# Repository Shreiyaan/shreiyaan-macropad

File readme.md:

Shreiyaan’s Macropad

This is a three-key macropad with a rotary encoder. I made it for simple media controls and shortcuts that I use regularly. I designed the PCB in KiCad, made the enclosure in Fusion 360, and prepared the firmware using QMK.

The macropad uses a Seeed Studio XIAO RP2040, three MX-style mechanical switches, and an EC11 rotary encoder with a push switch.

The three keys are used for speaker mute, play/pause, and Print Screen. Rotating the encoder changes the volume, and pressing the encoder toggles speaker mute.

I made the enclosure slightly larger so the macropad has a stable base and enough space around the controls to be comfortable on a desk. (and also, so i can design cool things on the case to make it look good)

Schematic:

PCB:

Enclosure:

The folder contains the KiCad schematic and PCB, Gerber and drill files, the STEP enclosure model, BOM, firmware source, compiled UF2 firmware, DRC report and project images.

The PCB DRC has 0 errors and 0 unconnected items. The remaining warnings are mostly related to silkscreen overlapping solder-mask areas.

The firmware has not been tested on assembled hardware yet. I will test the keys and encoder after the PCB is manufactured and assembled.

Use manufacturing_final.zip for PCB manufacturing. It contains the updated Gerber and drill files exported from Macropad_Checked.kicad_pcb. The other Gerber files and manufacturing ZIP are older versions.

Made by Shreiyaan P Shah.

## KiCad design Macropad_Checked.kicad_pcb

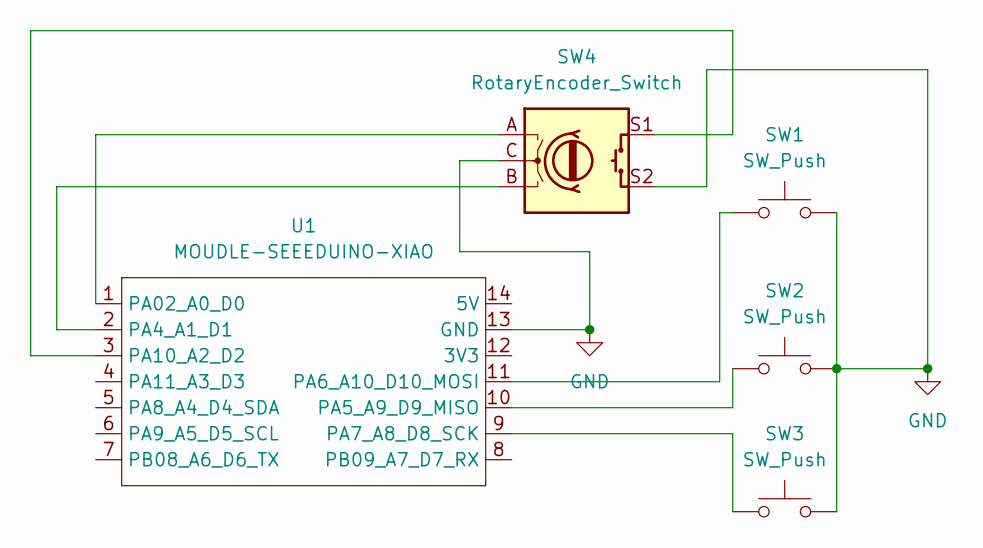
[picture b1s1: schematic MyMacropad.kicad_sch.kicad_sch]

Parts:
SW1, SW2, SW3: SW_Push; SW_Cherry_MX_1.00u_PCB
SW4: RotaryEncoder_Switch; RotaryEncoder_Alps_EC11E-Switch_Vertical_H20mm
U1: MOUDLE-SEEEDUINO-XIAO; XIAO-Generic-Hybrid-14P-2.54-21X17.8MM

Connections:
GND: SW1.2, SW2.2, SW3.2, SW4.C, SW4.S2, U1.13 (GND)
unnamed: SW4.A, U1.1 (PA02_A0_D0)
unnamed: SW4.B, U1.2 (PA4_A1_D1)
unnamed: SW2.1, U1.10 (PA5_A9_D9_MISO)
unnamed: SW1.1, U1.11 (PA6_A10_D10_MOSI)
unnamed: SW3.1, U1.9 (PA7_A8_D8_SCK)
unnamed: SW4.S1, U1.3 (PA10_A2_D2)

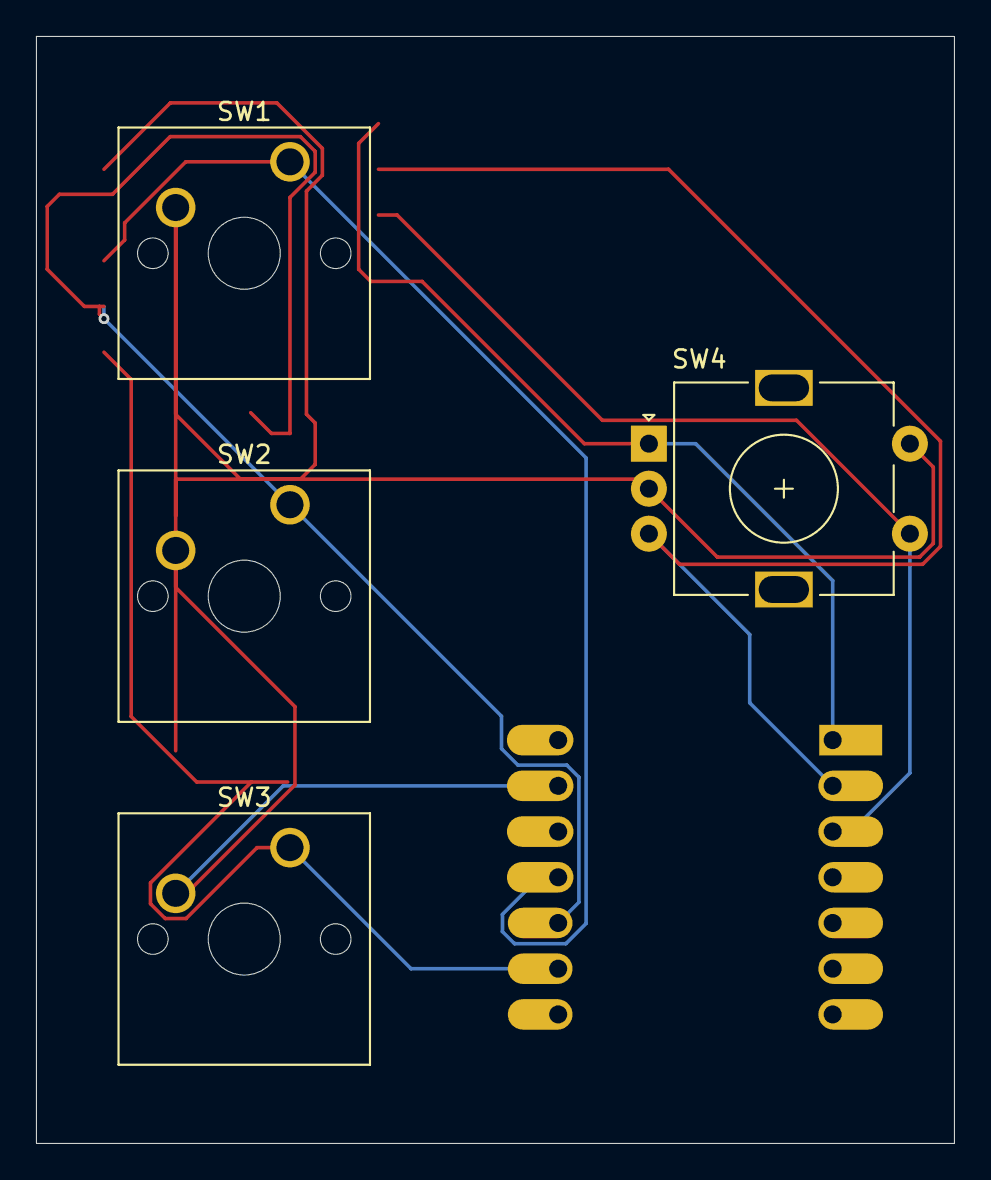
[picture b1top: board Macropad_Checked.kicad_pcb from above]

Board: 2 copper layers, 51.0 x 61.5 mm, 5 parts (1 on the bottom side), 7 nets.

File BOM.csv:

"Reference","Qty","Value","DNP","Exclude from BOM","Exclude from Board","Exclude from Simulation","Exclude from Position Files","Footprint","Datasheet"
"SW1,SW2,SW3","3","SW_Push","","","","","${EXCLUDE_FROM_POS_FILES}","Button_Switch_Keyboard:SW_Cherry_MX_1.00u_PCB",""
"SW4","1","RotaryEncoder_Switch","","","","","${EXCLUDE_FROM_POS_FILES}","Rotary_Encoder:RotaryEncoder_Alps_EC11E-Switch_Vertical_H20mm",""
"U1","1","MOUDLE-SEEEDUINO-XIAO","","","","","${EXCLUDE_FROM_POS_FILES}","footprints:XIAO-Generic-Hybrid-14P-2.54-21X17.8MM",""
